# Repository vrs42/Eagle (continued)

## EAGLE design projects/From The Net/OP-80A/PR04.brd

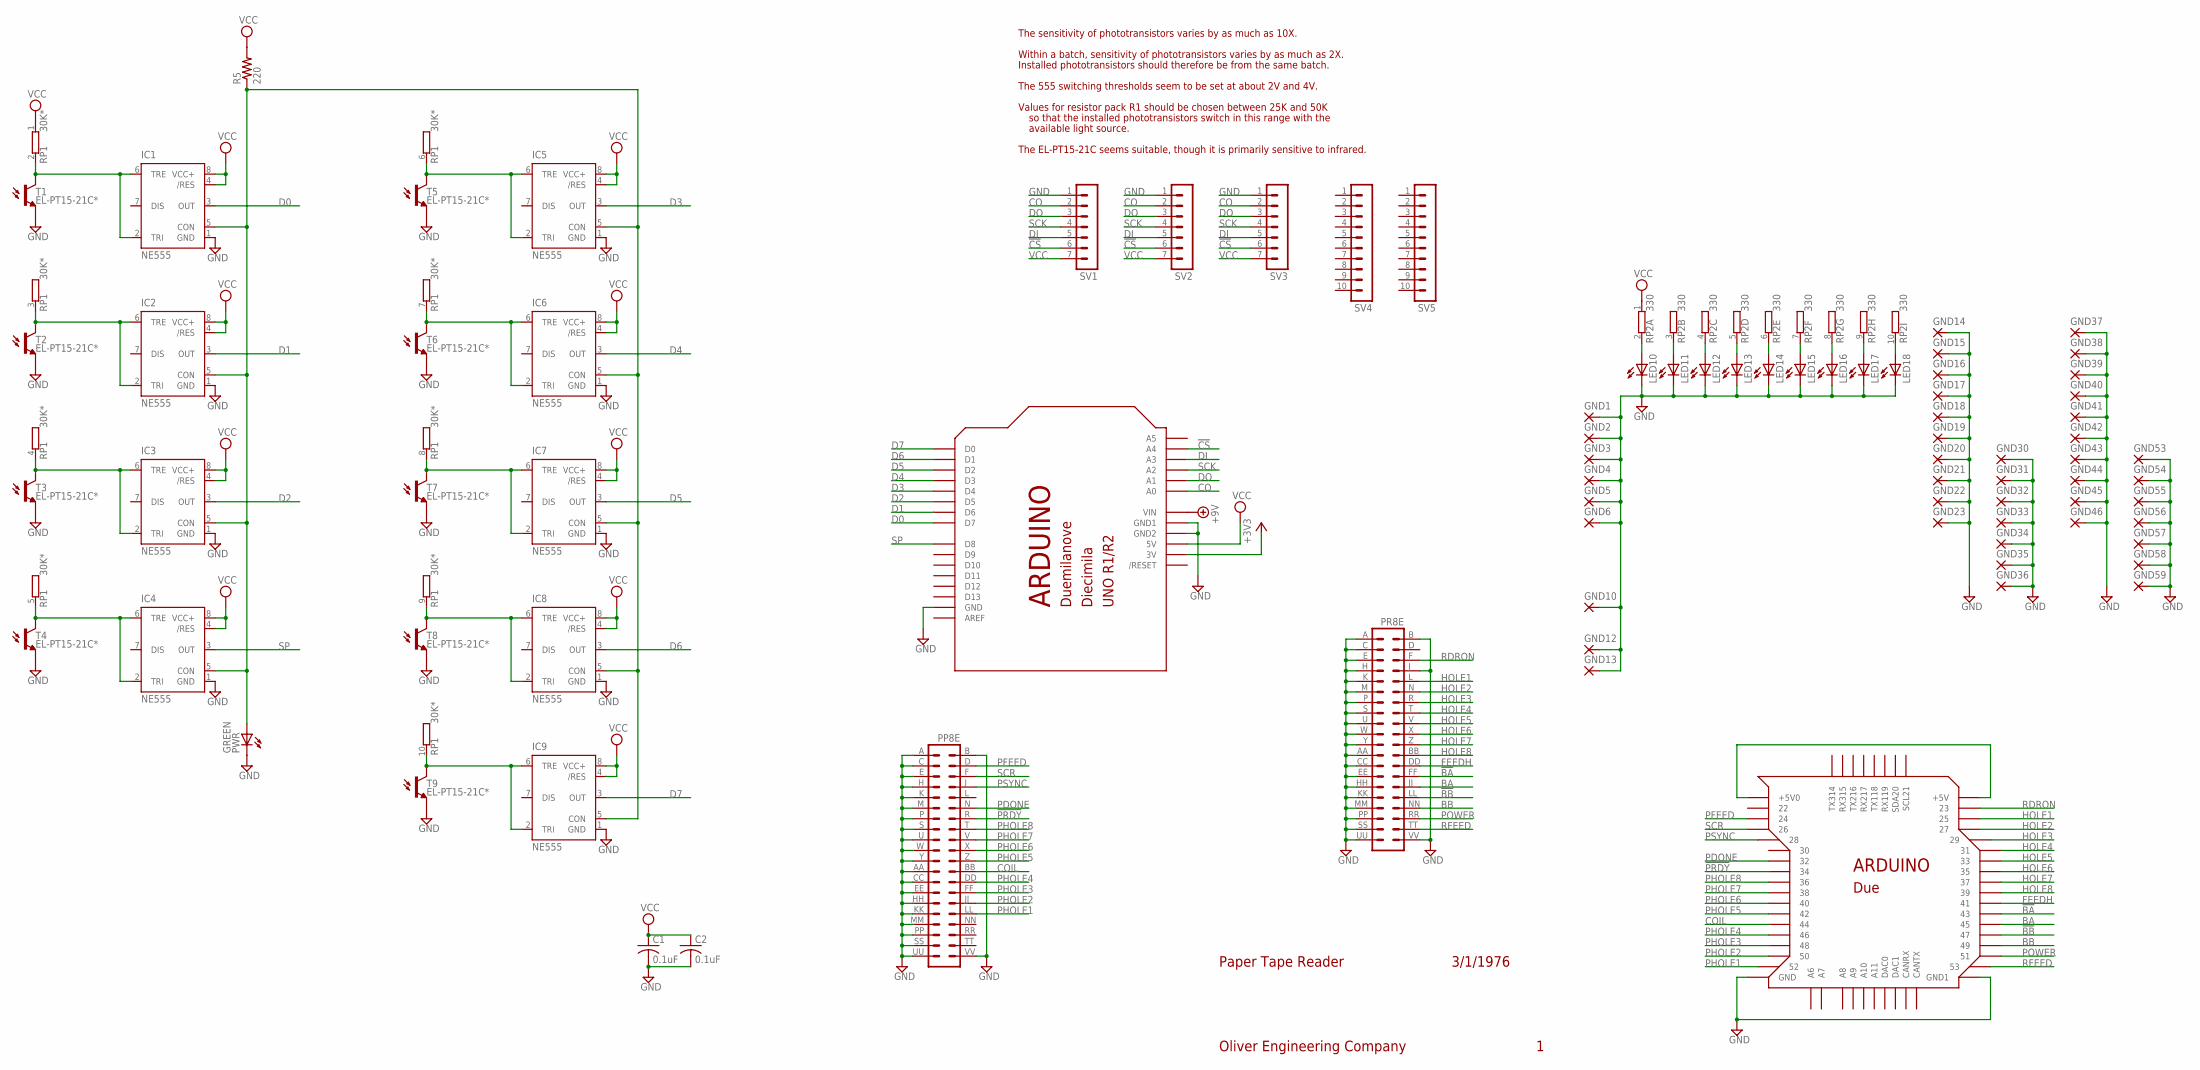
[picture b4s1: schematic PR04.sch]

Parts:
C1, C2: 0.1uF; C050-030X075
GND1, GND2, GND3, GND4, GND5, GND6, GND10, GND12, GND13, GND14, GND15, GND16, GND17, GND18, GND19, GND20, GND21, GND22, GND23, GND30, GND31, GND32, GND33, GND34, GND35, GND36, GND37, GND38, GND39, GND40, GND41, GND42, GND43, GND44, GND45, GND46, GND53, GND54, GND55, GND56, GND57, GND58, GND59: 2,15/1,0
IC1, IC2, IC3, IC4, IC5, IC6, IC7, IC8, IC9: NE555; DIL-08
LED10, LED11, LED12, LED13, LED14, LED15, LED16, LED17, LED18: LEDCHIPLED_1206; CHIPLED_1206
PP8E: DEC40PINV
PR8E: DEC40PINV
PWR: GREEN; LED3MM
R5: 220; 0207/10
RP1: 30K*; SIL10
RP2: 330; SIL10
SV1, SV2, SV3: MA07-1
SV4, SV5: MA10-1
T1, T2, T3, T4, T5, T6, T7, T8, T9: EL-PT15-21C*; CHIPLED_1206
U$2: ARDUINO-X; ARDUINO_DUE_SHIELD

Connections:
!BA: PR8E.FF (28), U$2.43
!BB: PR8E.LL (32), U$2.47
!CS: SV1.6, SV2.6, SV3.6, U$2.A4
!PRDY: PP8E.R (14), U$2.34
+3V3: U$2.3V3 (3V)
+5V: U$2.5V0_1 (+5V), U$2.5V0_2 (+5V0)
+9V: U$2.VIN
BA: PR8E.JJ (30), U$2.45
BB: PR8E.NN (34), U$2.49
CO: SV1.2, SV2.2, SV3.2, U$2.A0
COIL: PP8E.BB (24), U$2.44
D0: IC1.3 (OUT), U$2.7 (D7)
D1: IC2.3 (OUT), U$2.6 (D6)
D2: IC3.3 (OUT), U$2.5 (D5)
D3: IC5.3 (OUT), U$2.4 (D4)
D4: IC6.3 (OUT), U$2.3 (D3)
D5: IC7.3 (OUT), U$2.2 (D2)
D6: IC8.3 (OUT), U$2.1 (D1)
D7: IC9.3 (OUT), U$2.0 (D0)
DI: SV1.5, SV2.5, SV3.5, U$2.A3
DO: SV1.3, SV2.3, SV3.3, U$2.A1
FEEDH: PR8E.DD (26), U$2.41
GND: C1.2, C2.2, GND1.1, GND2.1, GND3.1, GND4.1, GND5.1, GND6.1, GND10.1, GND12.1, GND13.1, GND14.1, GND15.1, GND16.1, GND17.1, GND18.1, GND19.1, GND20.1, GND21.1, GND22.1, GND23.1, GND30.1, GND31.1, GND32.1, GND33.1, GND34.1, GND35.1, GND36.1, GND37.1, GND38.1, GND39.1, GND40.1, GND41.1, GND42.1, GND43.1, GND44.1, GND45.1, GND46.1, GND53.1, GND54.1, GND55.1, GND56.1, GND57.1, GND58.1, GND59.1, IC1.1 (GND), IC2.1 (GND), IC3.1 (GND), IC4.1 (GND), IC5.1 (GND), IC6.1 (GND), IC7.1 (GND), IC8.1 (GND), IC9.1 (GND), LED10.C, LED11.C, LED12.C, LED13.C, LED14.C, LED15.C, LED16.C, LED17.C, LED18.C, PP8E.A (1), PP8E.AA (23), PP8E.B (2), PP8E.C (3), PP8E.CC (25), PP8E.E (5), PP8E.EE (27), PP8E.H (7), PP8E.HH (29), PP8E.K (9), PP8E.KK (31), PP8E.M (11), PP8E.MM (33), PP8E.P (13), PP8E.PP (35), PP8E.S (15), PP8E.SS (37), PP8E.U (17), PP8E.UU (39), PP8E.VV (40), PP8E.W (19), PP8E.Y (21), PR8E.A (1), PR8E.AA (23), PR8E.B (2), PR8E.C (3), PR8E.CC (25), PR8E.E (5), PR8E.EE (27), PR8E.H (7), PR8E.HH (29), PR8E.J (8), PR8E.K (9), PR8E.KK (31), PR8E.M (11), PR8E.MM (33), PR8E.P (13), PR8E.PP (35), PR8E.S (15), PR8E.SS (37), PR8E.U (17), PR8E.UU (39), PR8E.VV (40), PR8E.W (19), PR8E.Y (21), PWR.K (C), SV1.1, SV2.1, SV3.1, T1.C (E), T2.C (E), T3.C (E), T4.C (E), T5.C (E), T6.C (E), T7.C (E), T8.C (E), T9.C (E), U$2.GND, U$2.GND_1 (GND1), U$2.GND_2 (GND2), U$2.GND_3 (GND), U$2.GND_4 (GND1)
HOLE1: PR8E.L (10), U$2.25
HOLE2: PR8E.N (12), U$2.27
HOLE3: PR8E.R (14), U$2.29
HOLE4: PR8E.T (16), U$2.31
HOLE5: PR8E.V (18), U$2.33
HOLE6: PR8E.X (20), U$2.35
HOLE7: PR8E.Z (22), U$2.37
HOLE8: PR8E.BB (24), U$2.39
unnamed: IC1.2 (TRI), IC1.6 (TRE), RP1.2, T1.A (C)
unnamed: IC1.5 (CON), IC2.5 (CON), IC3.5 (CON), IC4.5 (CON), IC5.5 (CON), IC6.5 (CON), IC7.5 (CON), IC8.5 (CON), IC9.5 (CON), PWR.A, R5.1
unnamed: IC2.2 (TRI), IC2.6 (TRE), RP1.3 (2), T2.A (C)
unnamed: IC3.2 (TRI), IC3.6 (TRE), RP1.4 (2), T3.A (C)
unnamed: IC9.2 (TRI), IC9.6 (TRE), RP1.10 (2), T9.A (C)
unnamed: IC4.2 (TRI), IC4.6 (TRE), RP1.5 (2), T4.A (C)
unnamed: LED10.A, RP2.2
unnamed: IC5.2 (TRI), IC5.6 (TRE), RP1.6 (2), T5.A (C)
unnamed: LED13.A, RP2.5 (2)
unnamed: IC6.2 (TRI), IC6.6 (TRE), RP1.7 (2), T6.A (C)
unnamed: IC7.2 (TRI), IC7.6 (TRE), RP1.8 (2), T7.A (C)
unnamed: IC8.2 (TRI), IC8.6 (TRE), RP1.9 (2), T8.A (C)
unnamed: LED16.A, RP2.8 (2)
unnamed: LED18.A, RP2.10 (2)
unnamed: LED17.A, RP2.9 (2)
unnamed: LED15.A, RP2.7 (2)
unnamed: LED14.A, RP2.6 (2)
unnamed: LED12.A, RP2.4 (2)
unnamed: LED11.A, RP2.3 (2)
PDONE: PP8E.N (12), U$2.32
PFEED: PP8E.D (4), U$2.24
PHOLE1: PP8E.LL (32), U$2.52
PHOLE2: PP8E.JJ (30), U$2.50
PHOLE3: PP8E.FF (28), U$2.48
PHOLE4: PP8E.DD (26), U$2.46
PHOLE5: PP8E.Z (22), U$2.42
PHOLE6: PP8E.X (20), U$2.40
PHOLE7: PP8E.V (18), U$2.38
PHOLE8: PP8E.T (16), U$2.36
POWER: PR8E.RR (36), U$2.51
PSYNC: PP8E.J (8), U$2.28
RDRON: PR8E.F (6), U$2.23
RFEED: PR8E.TT (38), U$2.53
SCK: SV1.4, SV2.4, SV3.4, U$2.A2
SCR: PP8E.F (6), U$2.26
SP: IC4.3 (OUT), U$2.8 (D8)
VCC: C1.1, C2.1, IC1.4 (/RES), IC1.8 (VCC+), IC2.4 (/RES), IC2.8 (VCC+), IC3.4 (/RES), IC3.8 (VCC+), IC4.4 (/RES), IC4.8 (VCC+), IC5.4 (/RES), IC5.8 (VCC+), IC6.4 (/RES), IC6.8 (VCC+), IC7.4 (/RES), IC7.8 (VCC+), IC8.4 (/RES), IC8.8 (VCC+), IC9.4 (/RES), IC9.8 (VCC+), R5.2, RP1.1, RP2.1, SV1.7, SV2.7, SV3.7, U$2.5V0 (5V)

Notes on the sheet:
Oliver Engineering Company
Paper Tape Reader
3/1/1976
The sensitivity of phototransistors varies by as much as 10X.
Within a batch, sensitivity of phototransistors varies by as much as 2X.
The 555 switching thresholds seem to be set at about 2V and 4V.
Values for resistor pack R1 should be chosen between 25K and 50K
Installed phototransistors should therefore be from the same batch.
so that the installed phototransistors switch in this range with the
available light source.
The EL-PT15-21C seems suitable, though it is primarily sensitive to infrared.

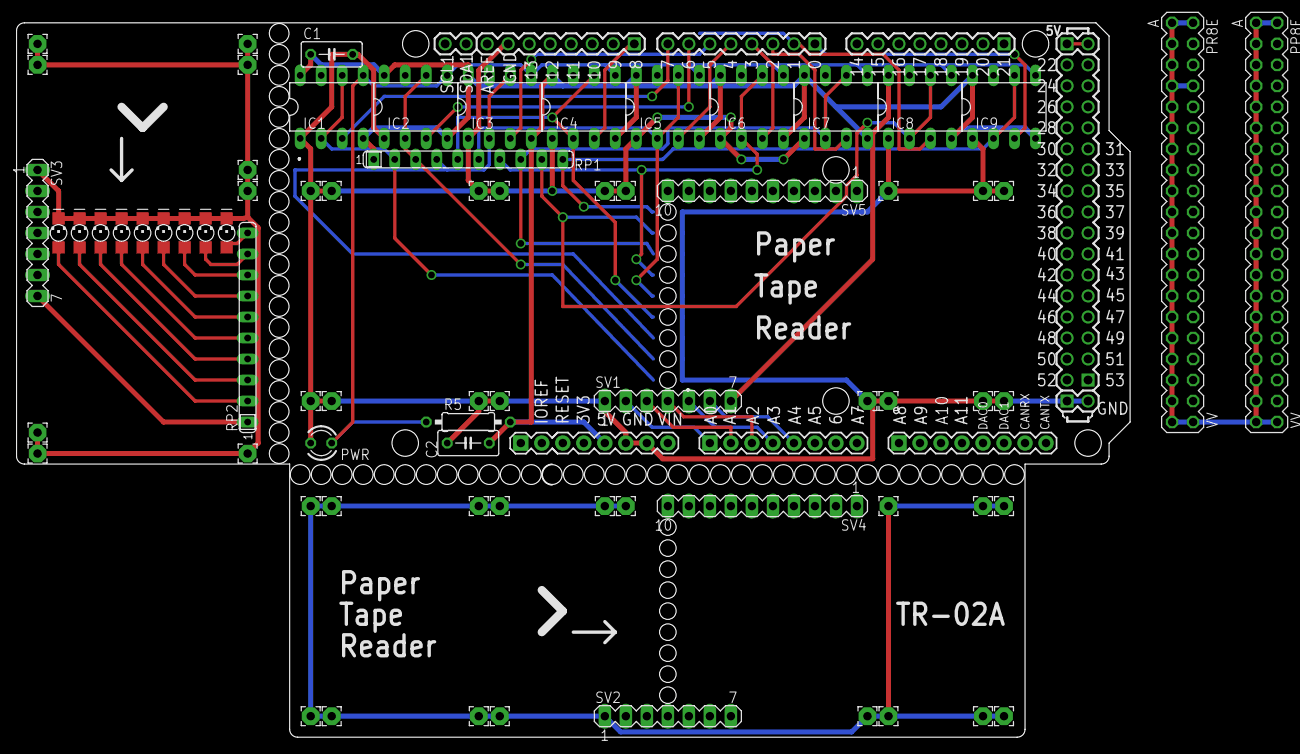
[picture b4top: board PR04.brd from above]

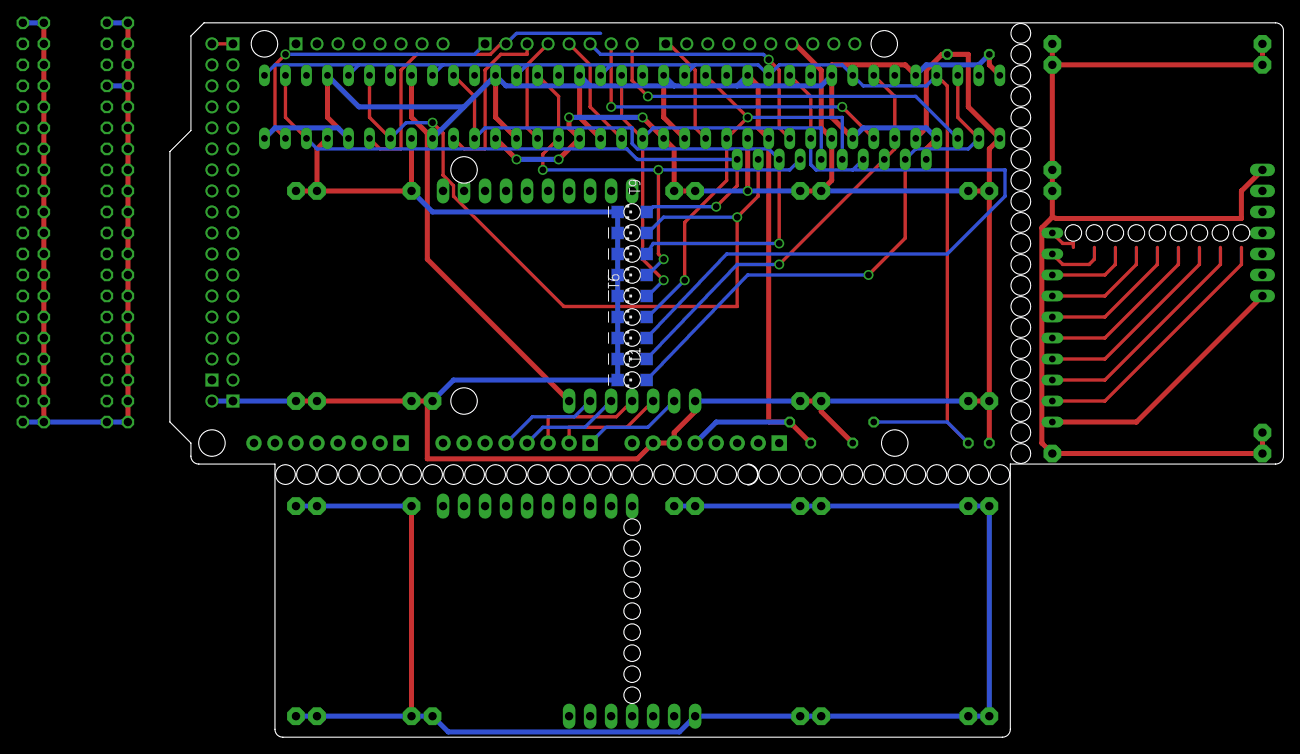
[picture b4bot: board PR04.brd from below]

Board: 2 copper layers, 134.6 x 86.4 mm, 84 parts (9 on the bottom side), 66 nets.

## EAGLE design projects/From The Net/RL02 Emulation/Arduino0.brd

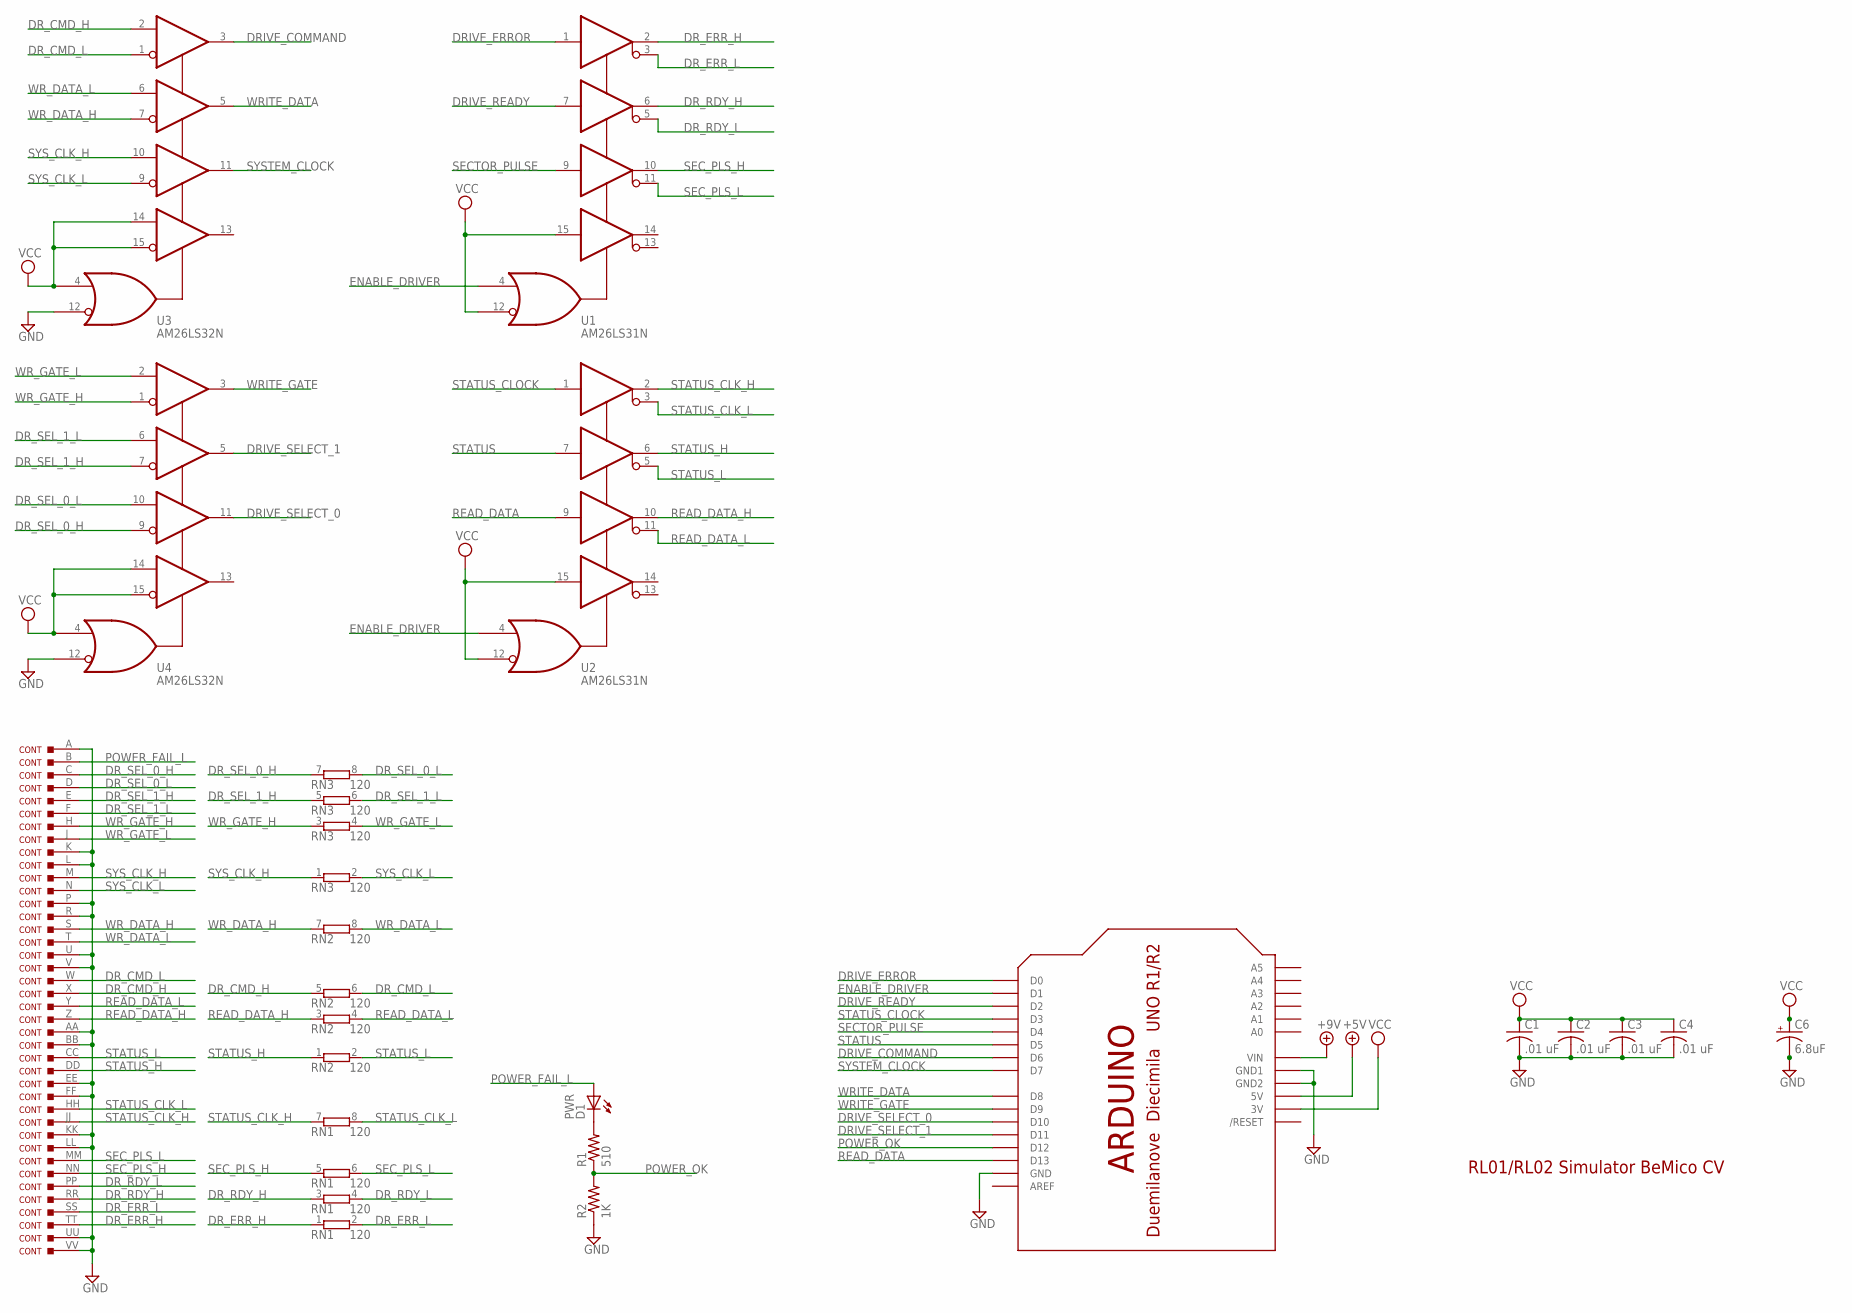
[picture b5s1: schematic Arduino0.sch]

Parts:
C1, C2, C3, C4: .01 uF; C050-025X075
C6: 6.8uF; E5-5
CONT: DEC40PINSV; DEC40PINV
D1: PWR; LED5MM
R1: 510; 0207/10
R2: 1K; 0207/10
RN1, RN2, RN3: 120; SIL8
U1, U2: AM26LS31N; DIL16
U3, U4: AM26LS32N; DIL16
U$3: ARDUINOUNO; ARDUINO

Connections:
+5V: U$3.5V
+9V: U$3.VIN
DRIVE_COMMAND: U3.3 (Y1), U$3.D6
DRIVE_ERROR: U1.1 (A1), U$3.D0
DRIVE_READY: U1.7 (A2), U$3.D2
DRIVE_SELECT_0: U4.11 (Y3), U$3.D10
DRIVE_SELECT_1: U4.5 (Y2), U$3.D11
DR_CMD_H: CONT.X, RN2.5 (1), U3.2 (P1)
DR_CMD_L: CONT.W, RN2.6 (2), U3.1 (N1)
DR_ERR_H: CONT.TT, RN1.1, U1.2 (Y1)
DR_ERR_L: CONT.SS, RN1.2, U1.3 (Z1)
DR_RDY_H: CONT.RR, RN1.3 (1), U1.6 (Y2)
DR_RDY_L: CONT.PP, RN1.4 (2), U1.5 (Z2)
DR_SEL_0_H: CONT.C, RN3.7 (1), U4.9 (N3)
DR_SEL_0_L: CONT.D, RN3.8 (2), U4.10 (P3)
DR_SEL_1_H: CONT.E, RN3.5 (1), U4.7 (N2)
DR_SEL_1_L: CONT.F, RN3.6 (2), U4.6 (P2)
ENABLE_DRIVER: U1.4 (G), U2.4 (G), U$3.D1
GND: C1.2, C2.2, C3.2, C4.2, C6.-, CONT.A, CONT.AA, CONT.BB, CONT.EE, CONT.FF, CONT.K, CONT.KK, CONT.L, CONT.LL, CONT.P, CONT.R, CONT.U, CONT.UU, CONT.V, CONT.VV, R2.1, U1.8 (GND), U2.8 (GND), U3.8 (GND), U3.12 (!G), U4.8 (GND), U4.12 (!G), U$3.GND, U$3.GND1, U$3.GND2
unnamed: D1.K (C), R1.2
POWER_FAIL_L: CONT.B, D1.A
POWER_OK: R1.1, R2.2, U$3.D12
READ_DATA: U2.9 (A3), U$3.D13
READ_DATA_H: CONT.Z, RN2.3 (1), U2.10 (Y3)
READ_DATA_L: CONT.Y, RN2.4 (2), U2.11 (Z3)
SECTOR_PULSE: U1.9 (A3), U$3.D4
SEC_PLS_H: CONT.NN, RN1.5 (1), U1.10 (Y3)
SEC_PLS_L: CONT.MM, RN1.6 (2), U1.11 (Z3)
STATUS: U2.7 (A2), U$3.D5
STATUS_CLK_H: CONT.JJ, RN1.7 (1), U2.2 (Y1)
STATUS_CLK_L: CONT.HH, RN1.8 (2), U2.3 (Z1)
STATUS_CLOCK: U2.1 (A1), U$3.D3
STATUS_H: CONT.DD, RN2.1, U2.6 (Y2)
STATUS_L: CONT.CC, RN2.2, U2.5 (Z2)
SYSTEM_CLOCK: U3.11 (Y3), U$3.D7
SYS_CLK_H: CONT.M, RN3.1, U3.10 (P3)
SYS_CLK_L: CONT.N, RN3.2, U3.9 (N3)
VCC: C1.1, C2.1, C3.1, C4.1, C6.+, U1.12 (!G), U1.15 (A4), U1.16 (VCC), U2.12 (!G), U2.15 (A4), U2.16 (VCC), U3.4 (G), U3.14 (P4), U3.15 (N4), U3.16 (VCC), U4.4 (G), U4.14 (P4), U4.15 (N4), U4.16 (VCC), U$3.3V
WRITE_DATA: U3.5 (Y2), U$3.D8
WRITE_GATE: U4.3 (Y1), U$3.D9
WR_DATA_H: CONT.S, RN2.7 (1), U3.7 (N2)
WR_DATA_L: CONT.T, RN2.8 (2), U3.6 (P2)
WR_GATE_H: CONT.H, RN3.3 (1), U4.1 (N1)
WR_GATE_L: CONT.J, RN3.4 (2), U4.2 (P1)

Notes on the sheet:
RL01/RL02 Simulator BeMico CV

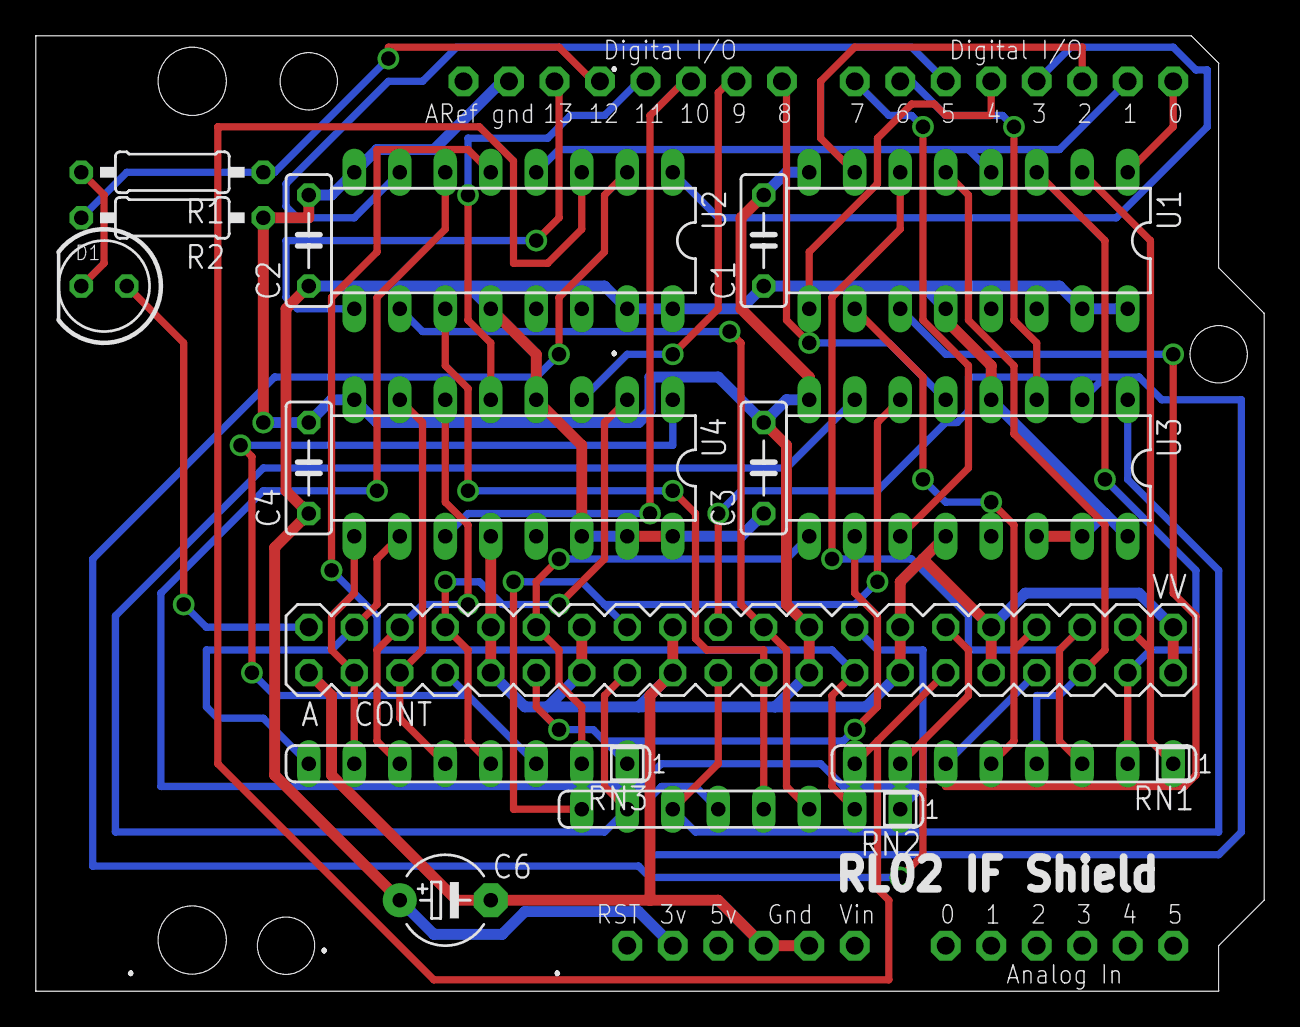
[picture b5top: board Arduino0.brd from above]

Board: 2 copper layers, 68.6 x 53.3 mm, 17 parts (0 on the bottom side), 42 nets.
